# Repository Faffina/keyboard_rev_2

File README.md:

pcb and 3d parts for a custo keyboard

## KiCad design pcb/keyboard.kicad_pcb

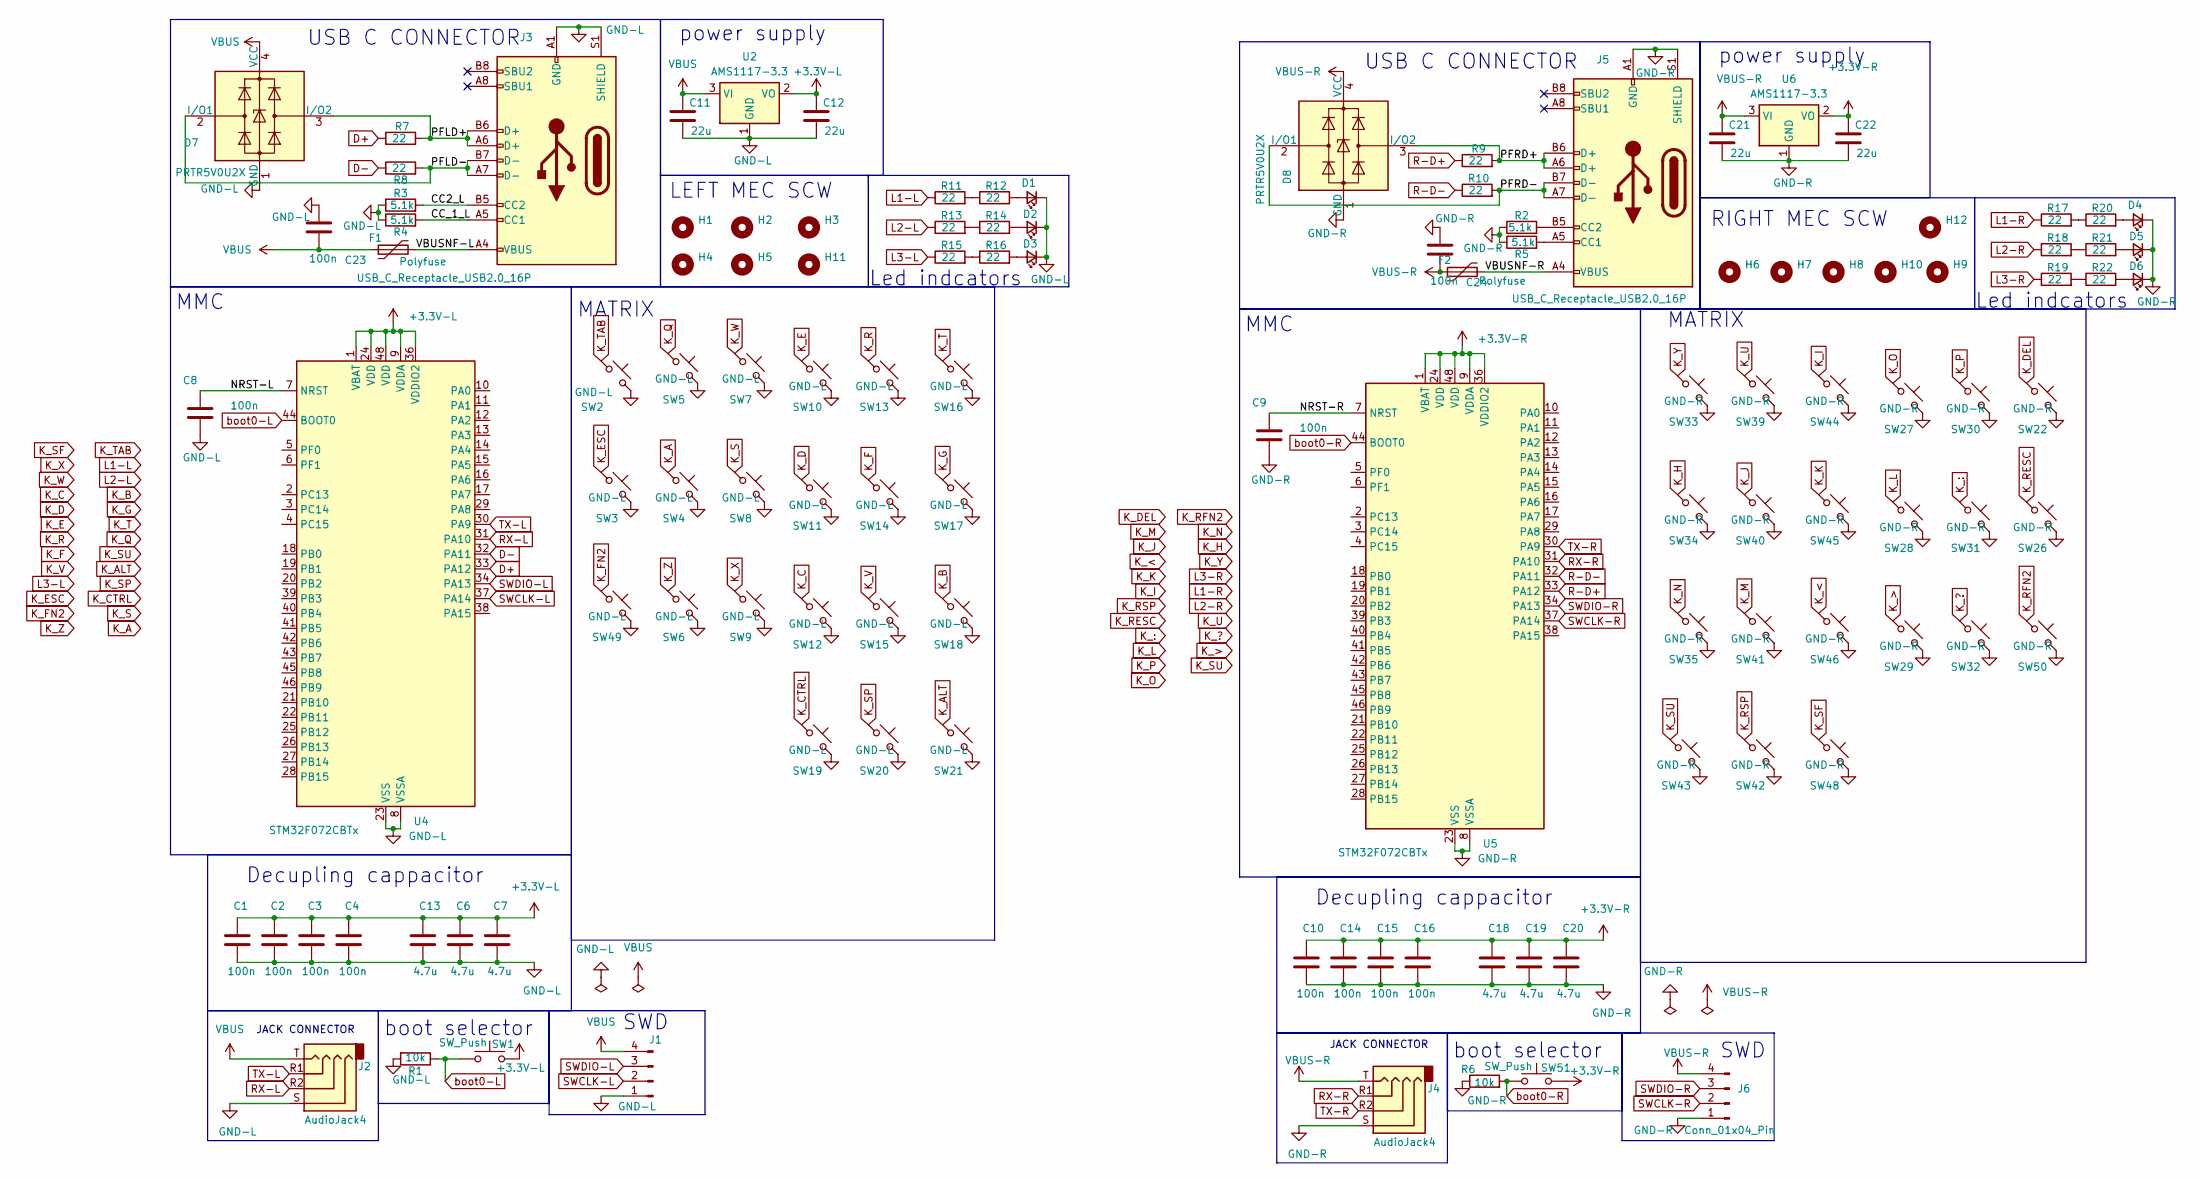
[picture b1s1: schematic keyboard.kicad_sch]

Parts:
C1, C2, C3, C4, C8, C9, C10, C14, C15, C16, C23, C24: 100n; C_0603_1608Metric
C6, C7, C13, C18, C19, C20: 4.7u; C_1206_3216Metric
C11, C12, C21, C22: 22u; C_0603_1608Metric
D1, D2, D3, D4, D5, D6: LED_Small; LED_0603_1608Metric
D7, D8: PRTR5V0U2X; SOT-143
F1, F2: Polyfuse; C_1812_4532Metric
H1, H2, H3, H4, H5, H6, H7, H8, H9, H10, H11, H12: MountingHole; MountingHole_2mm
J1, J6: Conn_01x04_Pin; PinHeader_1x04_P2.54mm_Vertical
J2, J4: AudioJack4; Jack_3.5mm_PJ31060-I_Horizontal
J3, J5: USB_C_Receptacle_USB2.0_16P; USB_C_Receptacle_HRO_TYPE-C-31-M-12
R1, R6: 10k; R_0603_1608Metric
R2, R3, R4, R5: 5.1k; R_0603_1608Metric
R7, R8, R9, R10, R11, R12, R13, R14, R15, R16, R17, R18, R19, R20, R21, R22: 22; R_0603_1608Metric
SW1, SW51: SW_Push; SW_SPST_B3U-1000P
SW2, SW3, SW4, SW5, SW6, SW7, SW8, SW9, SW10, SW11, SW12, SW13, SW14, SW15, SW16, SW17, SW18, SW19, SW20, SW21, SW22, SW26, SW27, SW28, SW29, SW30, SW31, SW32, SW33, SW34, SW35, SW39, SW40, SW41, SW42, SW43, SW44, SW45, SW46, SW48, SW49, SW50: SW_Push_45deg; SW_choc_v1_HS_CPG135001S30_1u
U2, U6: AMS1117-3.3; SOT-223-3_TabPin2
U4, U5: STM32F072CBTx; LQFP-48_7x7mm_P0.5mm

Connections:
+3.3V-L: C1.1, C2.1, C3.1, C4.1, C6.1, C7.1, C12.1, C13.1, SW1.2, U2.2 (VO), U4.1 (VBAT), U4.9 (VDDA), U4.24 (VDD), U4.36 (VDDIO2), U4.48 (VDD)
+3.3V-R: C10.1, C14.1, C15.1, C16.1, C18.1, C19.1, C20.1, C22.1, SW51.2, U5.1 (VBAT), U5.9 (VDDA), U5.24 (VDD), U5.36 (VDDIO2), U5.48 (VDD), U6.2 (VO)
/CC2_L: J3.B5 (CC2), R3.2
/CC_1_L: J3.A5 (CC1), R4.2
/NRST-L: C8.1, U4.7 (NRST)
/NRST-R: C9.1, U5.7 (NRST)
/PFLD+: D7.3 (I/O2), J3.A6 (D+), J3.B6 (D+), R7.2
/PFLD-: D7.2 (I/O1), J3.A7 (D-), J3.B7 (D-), R8.2
/PFRD+: D8.3 (I/O2), J5.A6 (D+), J5.B6 (D+), R9.2
/PFRD-: D8.2 (I/O1), J5.A7 (D-), J5.B7 (D-), R10.2
/VBUSNF-L: F1.2, J3.A4 (VBUS), J3.A9 (VBUS), J3.B4 (VBUS), J3.B9 (VBUS)
/VBUSNF-R: F2.2, J5.A4 (VBUS), J5.A9 (VBUS), J5.B4 (VBUS), J5.B9 (VBUS)
D+: R7.1, U4.33 (PA12)
D-: R8.1, U4.32 (PA11)
GND-L: C1.2, C2.2, C3.2, C4.2, C6.2, C7.2, C8.2, C11.2, C12.2, C13.2, C23.1, D1.1 (K), D2.1 (K), D3.1 (K), D7.1 (GND), J1.1, J2.S, J3.A1 (GND), J3.A12 (GND), J3.B1 (GND), J3.B12 (GND), J3.S1 (SHIELD), R1.2, R3.1, R4.1, SW2.2, SW3.2, SW4.2, SW5.2, SW6.2, SW7.2, SW8.2, SW9.2, SW10.2, SW11.2, SW12.2, SW13.2, SW14.2, SW15.2, SW16.2, SW17.2, SW18.2, SW19.2, SW20.2, SW21.2, SW49.2, U2.1 (GND), U4.8 (VSSA), U4.23 (VSS), U4.35 (VSS), U4.47 (VSS)
GND-R: C9.2, C10.2, C14.2, C15.2, C16.2, C18.2, C19.2, C20.2, C21.2, C22.2, C24.1, D4.1 (K), D5.1 (K), D6.1 (K), D8.1 (GND), J4.S, J5.A1 (GND), J5.A12 (GND), J5.B1 (GND), J5.B12 (GND), J5.S1 (SHIELD), J6.1, R2.1, R5.1, R6.1, SW22.2, SW26.2, SW27.2, SW28.2, SW29.2, SW30.2, SW31.2, SW32.2, SW33.2, SW34.2, SW35.2, SW39.2, SW40.2, SW41.2, SW42.2, SW43.2, SW44.2, SW45.2, SW46.2, SW48.2, SW50.2, U5.8 (VSSA), U5.23 (VSS), U5.35 (VSS), U5.47 (VSS), U6.1 (GND)
K_:: SW31.1
K_<: SW46.1
K_>: SW29.1
K_?: SW32.1
K_A: SW4.1
K_ALT: SW21.1
K_B: SW18.1
K_C: SW12.1
K_CTRL: SW19.1
K_D: SW11.1
K_DEL: SW22.1
K_E: SW10.1
K_ESC: SW3.1
K_F: SW14.1
K_FN2: SW49.1
K_G: SW17.1
K_H: SW34.1
K_I: SW44.1
K_J: SW40.1
K_K: SW45.1
K_L: SW28.1
K_M: SW41.1
K_N: SW35.1
K_O: SW27.1
K_P: SW30.1
K_Q: SW5.1
K_R: SW13.1
K_RESC: SW26.1
K_RFN2: SW50.1
K_RSP: SW42.1
K_S: SW8.1
K_SF: SW48.1
K_SP: SW20.1
K_SU: SW43.1
K_T: SW16.1
K_TAB: SW2.1
K_U: SW39.1
K_V: SW15.1
K_W: SW7.1
K_X: SW9.1
K_Y: SW33.1
K_Z: SW6.1
L1-L: R11.1
L1-R: R17.1
L2-L: R13.1
L2-R: R18.1
L3-L: R15.1
L3-R: R19.1
unnamed: D1.2 (A), R12.2
unnamed: D2.2 (A), R14.2
unnamed: D3.2 (A), R16.2
unnamed: D4.2 (A), R20.2
unnamed: D5.2 (A), R21.2
unnamed: D6.2 (A), R22.2
unnamed: J5.A5 (CC1), R5.2
unnamed: J5.B5 (CC2), R2.2
unnamed: R11.2, R12.1
unnamed: R13.2, R14.1
unnamed: R15.2, R16.1
unnamed: R17.2, R20.1
unnamed: R18.2, R21.1
unnamed: R19.2, R22.1
R-D+: R9.1, U5.33 (PA12)
R-D-: R10.1, U5.32 (PA11)
RX-L: J2.R2, U4.31 (PA10)
RX-R: J4.R1, U5.31 (PA10)
SWCLK-L: J1.2, U4.37 (PA14)
SWCLK-R: J6.2, U5.37 (PA14)
SWDIO-L: J1.3, U4.34 (PA13)
SWDIO-R: J6.3, U5.34 (PA13)
TX-L: J2.R1, U4.30 (PA9)
TX-R: J4.R2, U5.30 (PA9)
VBUS: C11.1, C23.2, D7.4 (VCC), F1.1, J1.4, J2.T, U2.3 (VI)
VBUS-R: C21.1, C24.2, D8.4 (VCC), F2.1, J4.T, J6.4, U6.3 (VI)
boot0-L: R1.1, SW1.1, U4.44 (BOOT0)
boot0-R: R6.2, SW51.1, U5.44 (BOOT0)

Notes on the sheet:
boot selector
Decupling cappacitor
power supply
MATRIX
Led indcators
JACK CONNECTOR
USB C CONNECTOR
SWD
LEFT MEC SCW
MMC
RIGHT MEC SCW

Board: 2 copper layers, 120 parts (42 on the bottom side), 44 nets, no tracks yet.

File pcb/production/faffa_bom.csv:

Designator,Footprint,Quantity,Value,LCSC Part #
"C1, C10, C14, C15, C16, C17, C2, C23, C24, C25, C26, C3, C4, C5, C8, C9",0603,16,100n,
"C11, C12, C21, C22",0603,4,22u,
"C13, C18, C19, C20, C6, C7",1206,6,4.7u,
"D1, D2, D3, D4, D5, D6",0603,6,LED_Small,
"D7, D8",SOT-143,2,PRTR5V0U2X,
"F1, F2",1812,2,Polyfuse,
"J1, J6",PinHeader_1x04_P2.54mm_Vertical,2,Conn_01x04_Pin,
"J2, J4",Jack_3.5mm_PJ31060-I_Horizontal,2,AudioJack4,
"J3, J5",USB_C_Receptacle_HRO_TYPE-C-31-M-12,2,USB_C_Receptacle_USB2.0_16P,
"R1, R6",0603,2,10k,
"R10, R11, R12, R13, R14, R15, R16, R17, R18, R19, R20, R21, R22, R7, R8, R9",0603,16,22,
"R2, R3, R4, R5",0603,4,5.1k,
"SW1, SW51",SW_SPST_B3U-1000P,2,SW_Push,
"SW10, SW11, SW12, SW13, SW14, SW15, SW16, SW17, SW18, SW19, SW20, SW21, SW22, SW23, SW24, SW26, SW27, SW28, SW29, SW3, SW30, SW31, SW32, SW33, SW34, SW35, SW36, SW37, SW39, SW4, SW40, SW41, SW42, SW43, SW44, SW45, SW46, SW47, SW48, SW49, SW5, SW50, SW6, SW7, SW8, SW9",SW_choc_v1_HS_CPG135001S30_1u,46,SW_Push_45deg,
"SW2, SW38",ROT_Alps_EC11E-Switch,2,RotaryEncoder_Switch,
"U2, U6",SOT-223-3_TabPin2,2,AMS1117-3.3,
"U4, U5",LQFP-48_7x7mm_P0.5mm,2,STM32F072CBTx,

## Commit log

2025-12-17 frist commit
2026-02-11 init work on rev 3
2026-02-11 pogresss
2026-02-11 pppp
